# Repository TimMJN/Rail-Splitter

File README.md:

# Rail Splitter

This is a circuit for creating a buffered virtual ground. It is useful for powering synth modules from a DC power supply. For example, I use mine in combination with a lab PSU set to 24V. An isolated power supply is preferable, such that the virtual ground can be connected to the PSU's earth. Depending on the BUF634 package selected, this circuit may provide up to 150 or 250 mA. This is plenty for testing of one or a few modules. Obviously, powering a complete synth is better done by other means.

The circuit has only a few components, it can easily be build on perfboard or stripboard. I have attached some photos from my build, per inspiration. 

For more information about virtual ground circuits, please have a look at this page: https://tangentsoft.net/elec/vgrounds.html.

# License
All designs in this repository are released under GPL-3.0 licence. Feel free to use and adapt them to your heart's desire. I only ask to refrain from mass-production and commercialisation of PCBs/modules, as I rely on PCB sales for funding new module designs. If you use (parts of) my designs in your own modules, please credit me on your schematics and PCBs to help users find the original creator. I call upon your good conscience to make fair use of my work shared here.

# Support
If you like the resources I have made available here, and wish to support the development of new modules, feel free to buy me a few components through a small donation. I mainly design modules for fun, but you probably already know it can be a costly endeavour. All small contributions help me, thank you very much!

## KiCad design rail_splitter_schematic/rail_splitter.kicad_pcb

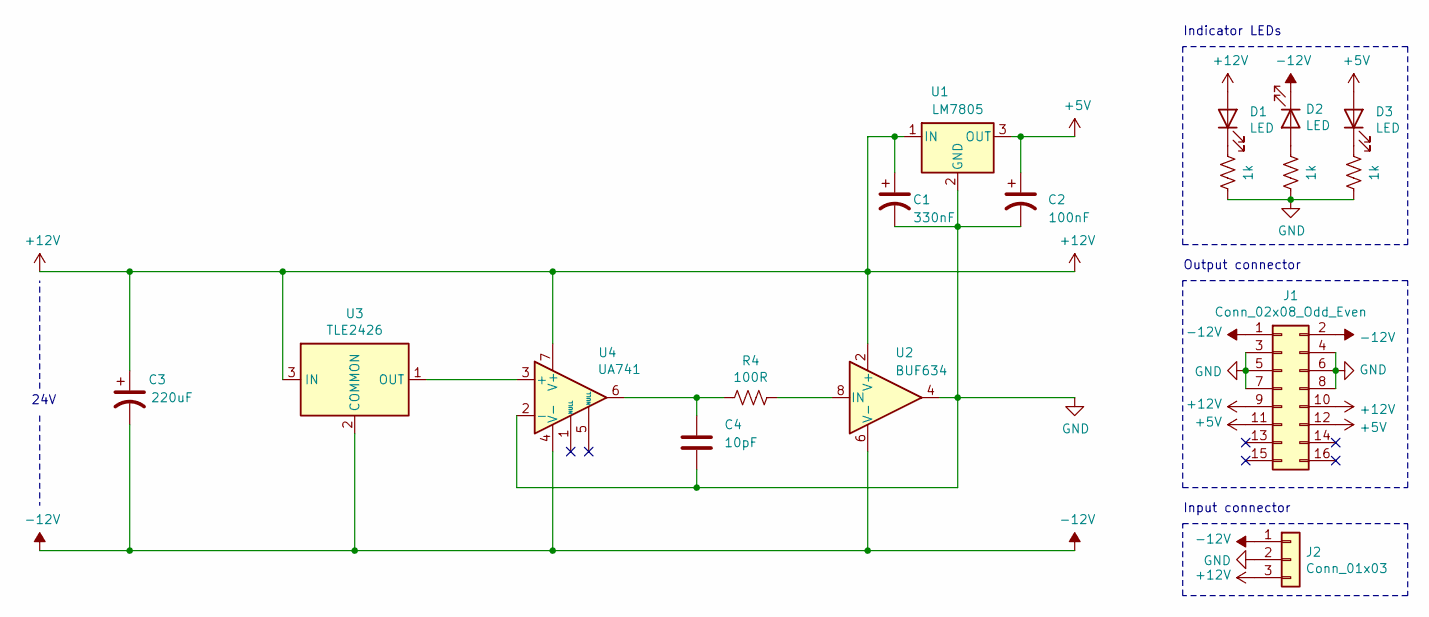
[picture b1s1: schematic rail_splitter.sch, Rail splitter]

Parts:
C1: 330nF; CP_Radial_D4.0mm_P2.00mm
C2: 100nF; CP_Radial_D4.0mm_P2.00mm
C3: 220uF; CP_Radial_D6.3mm_P2.50mm
C4: 10pF; C_Disc_D3.0mm_W2.0mm_P2.50mm
D1, D2, D3: LED; LED_D5.0mm
J1: Conn_02x08_Odd_Even; IDC-Header_2x08_P2.54mm_Vertical
J2: Conn_01x03; SolderWire-0.5sqmm_1x03_P4.8mm_D0.9mm_OD2.3mm_Relief
R1, R2, R3: 1k; R_Axial_DIN0207_L6.3mm_D2.5mm_P10.16mm_Horizontal
R4: 100R; R_Axial_DIN0207_L6.3mm_D2.5mm_P10.16mm_Horizontal
U1: LM7805; TO-220-3_Vertical
U2: BUF634; DIP-8_W7.62mm
U3: TLE2426; TO-92L_Inline
U4: UA741; DIP-8_W7.62mm

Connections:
+5V: C2.1, D3.2 (A), J1.11, J1.12, U1.3 (OUT); also elsewhere on the board
+12V: C1.1, C3.1, D1.2 (A), J1.9, J1.10, J2.3, U1.1 (IN), U2.2 (V+), U3.3 (IN), U4.7 (V+); also elsewhere on the board
-12V: C3.2, D2.1 (K), J1.1, J1.2, J2.1, U2.6 (V-), U3.2 (COMMON), U4.4 (V-); also elsewhere on the board
GND: C1.2, C2.2, C4.2, J1.3, J1.4, J1.5, J1.6, J1.7, J1.8, J2.2, R1.1, R2.1, R3.1, U1.2 (GND), U2.4, U4.2 (-); also elsewhere on the board
unnamed: C4.1, R4.2, U4.6
unnamed: D1.1 (K), R1.2
unnamed: D2.2 (A), R2.2
unnamed: D3.1 (K), R3.2
unnamed: R4.1, U2.8 (IN)
unnamed: U3.1 (OUT), U4.3 (+)

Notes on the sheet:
24V
Indicator LEDs
Output connector
Input connector

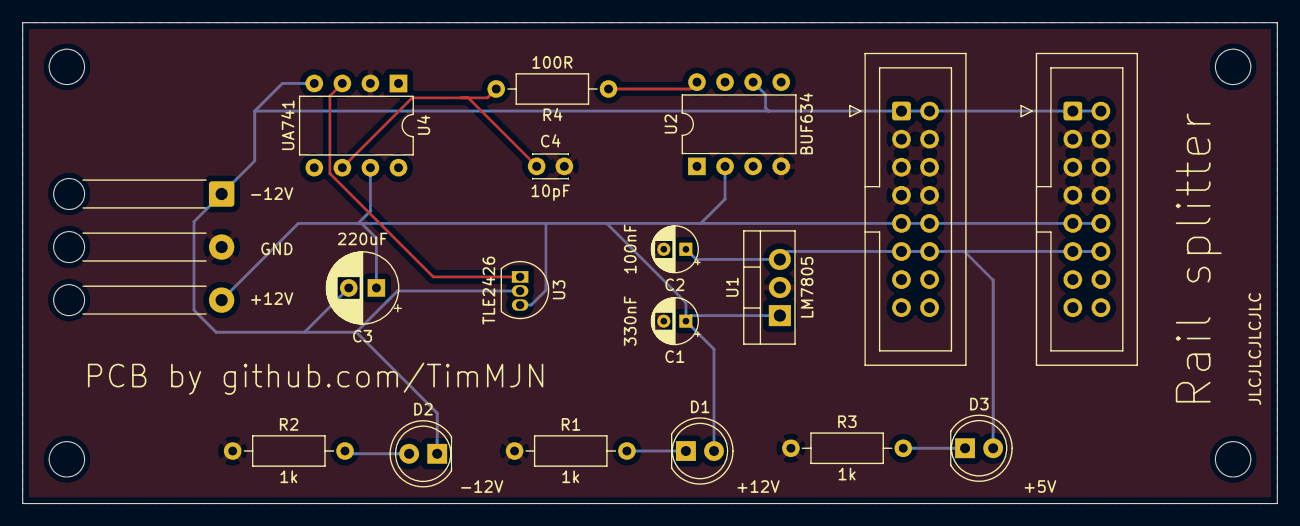
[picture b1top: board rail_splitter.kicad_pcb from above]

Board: 2 copper layers, 113.5 x 43.5 mm, 18 parts (0 on the bottom side), 10 nets.

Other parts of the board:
J1#2: Conn_02x08_Odd_Even; IDC-Header_2x08_P2.54mm_Vertical

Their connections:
+5V: J1#2.11, J1#2.12; also elsewhere on the board
+12V: J1#2.9, J1#2.10; also elsewhere on the board
-12V: J1#2.1, J1#2.2; also elsewhere on the board
GND: J1#2.3, J1#2.4, J1#2.5, J1#2.6, J1#2.7, J1#2.8; also elsewhere on the board

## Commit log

2020-12-16 Filles added
2021-01-16 remove KiCad files
2021-01-16 add URL
2021-01-16 added BOM
2021-01-16 removed lib file
2022-05-29 added datasheets
